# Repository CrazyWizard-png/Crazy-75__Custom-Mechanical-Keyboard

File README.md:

# Crazy-75
The journey of creating my first ever custom mechanical keyboard. 

Check my journal for the newest progress updates.

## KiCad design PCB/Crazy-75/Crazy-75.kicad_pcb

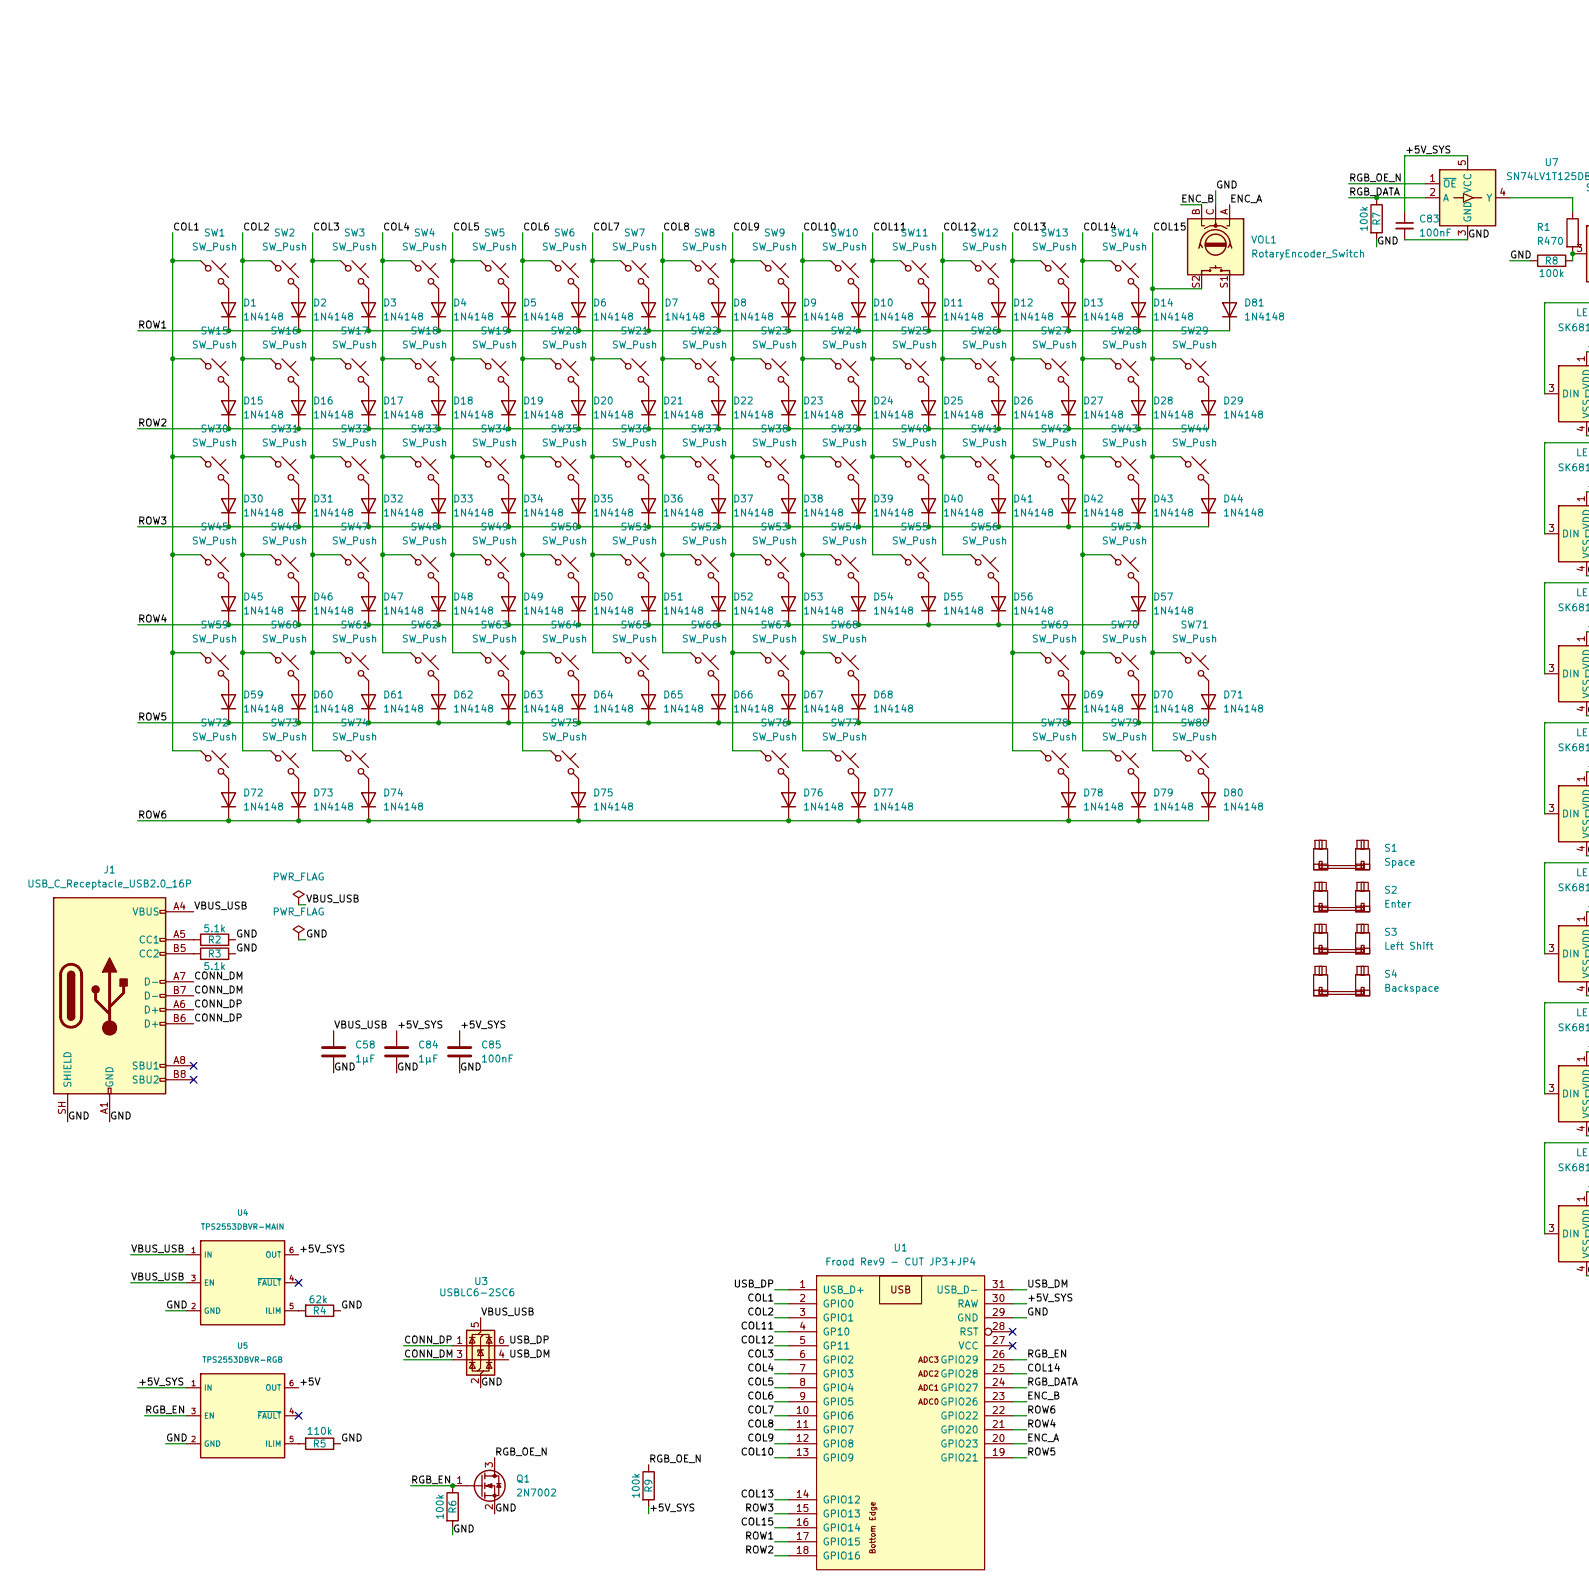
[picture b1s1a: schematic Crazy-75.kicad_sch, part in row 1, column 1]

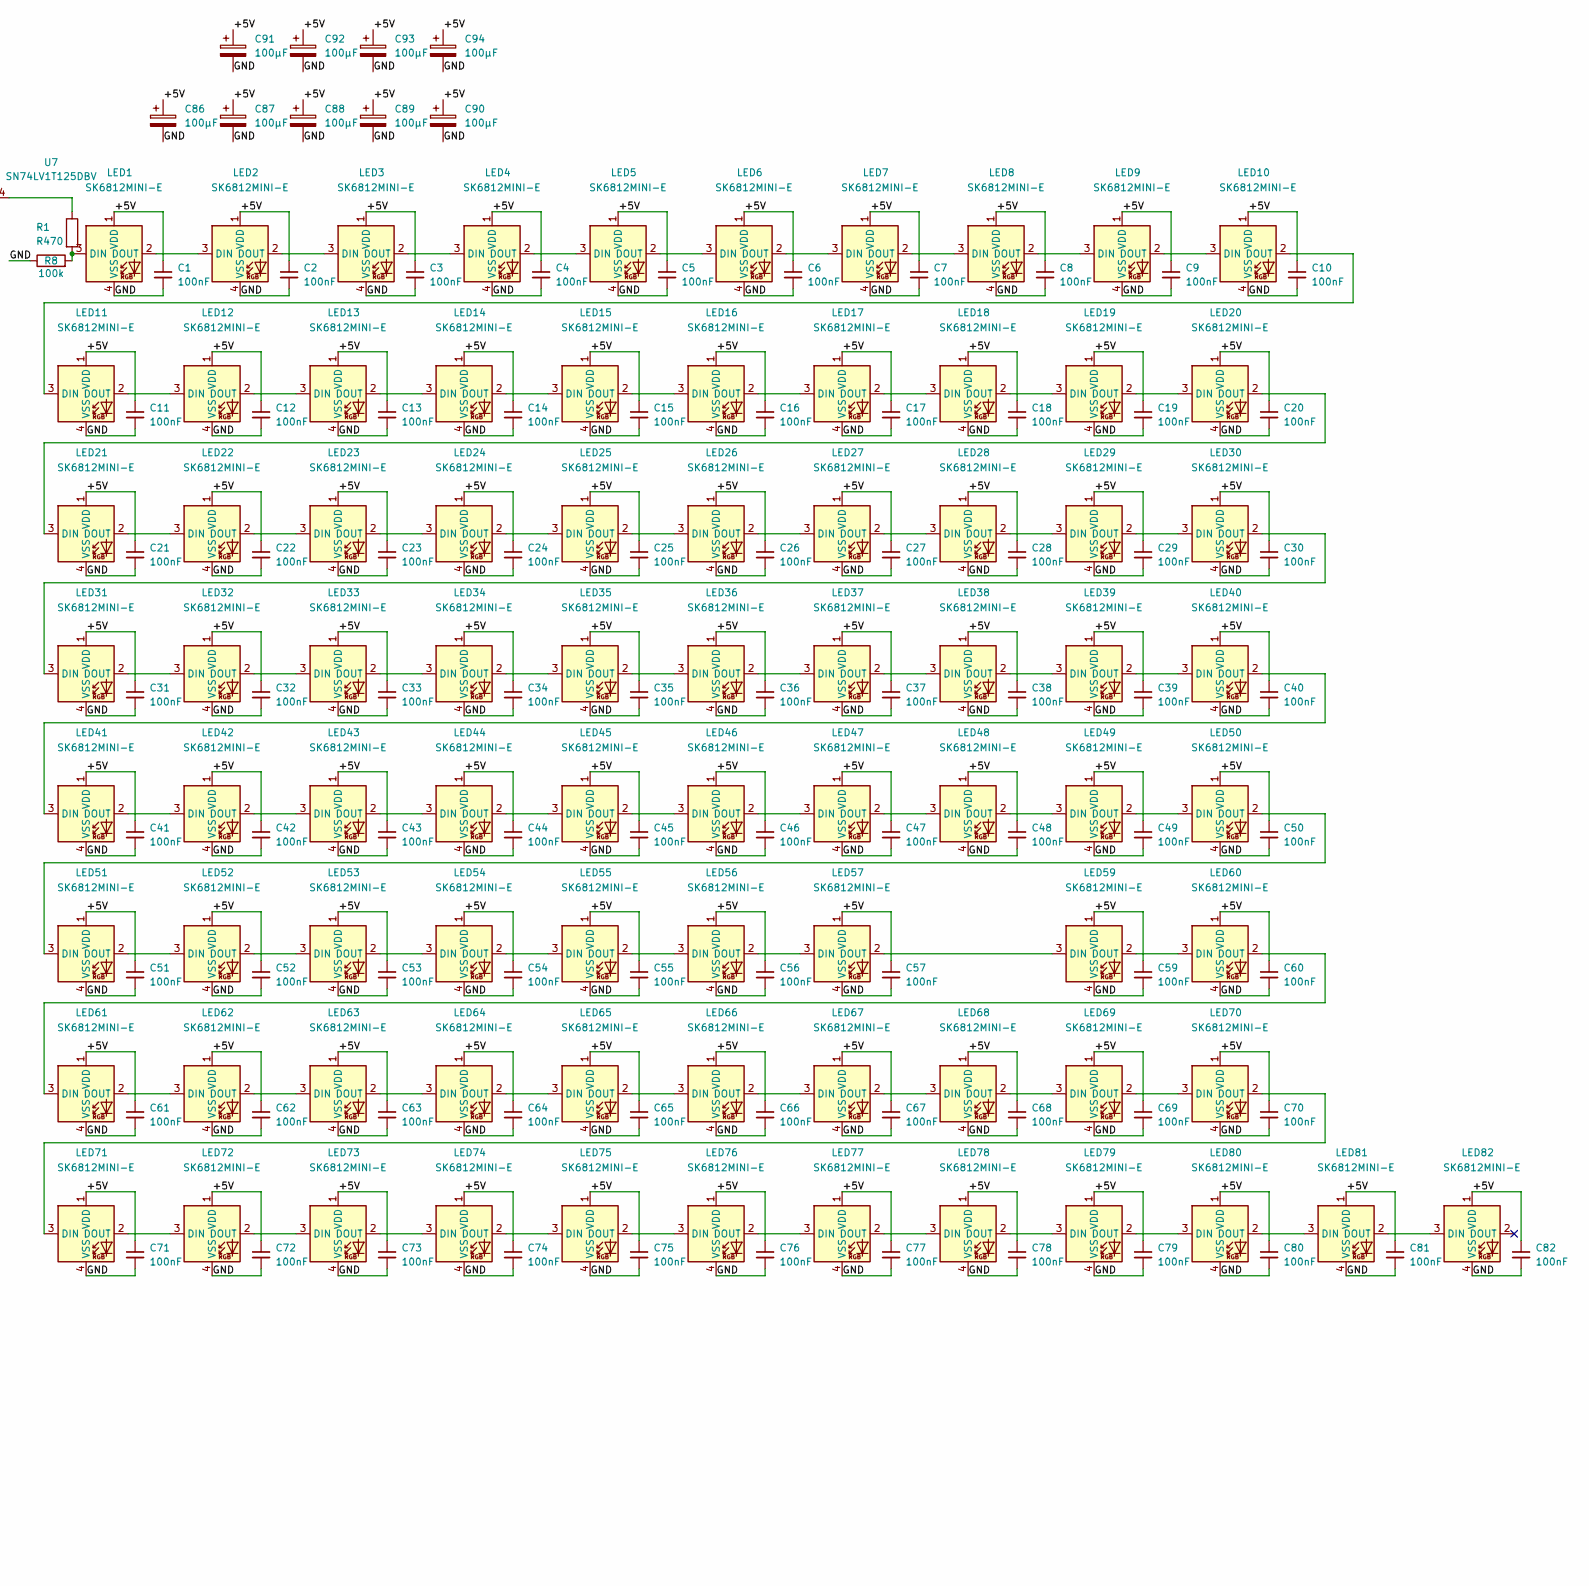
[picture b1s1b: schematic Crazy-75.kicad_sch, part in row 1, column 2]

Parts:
C1, C2, C3, C4, C5, C6, C7, C8, C9, C10, C11, C12, C13, C14, C15, C16, C17, C18, C19, C20, C21, C22, C23, C24, C25, C26, C27, C28, C29, C30, C31, C32, C33, C34, C35, C36, C37, C38, C39, C40, C41, C42, C43, C44, C45, C46, C47, C48, C49, C50, C51, C52, C53, C54, C55, C56, C57, C59, C60, C61, C62, C63, C64, C65, C66, C67, C68, C69, C70, C71, C72, C73, C74, C75, C76, C77, C78, C79, C80, C81, C82, C83, C85: 100nF; C_0805_2012Metric_Pad1.18x1.45mm_HandSolder
C58, C84: 1µF; C_0805_2012Metric_Pad1.18x1.45mm_HandSolder
C86, C87, C88, C89, C90, C91, C92, C93, C94: 100µF; CP_EIA-7343-31_Kemet-D_HandSolder
D1, D2, D3, D4, D5, D6, D7, D8, D9, D10, D11, D12, D13, D14, D15, D16, D17, D18, D19, D20, D21, D22, D23, D24, D25, D26, D27, D28, D29, D30, D31, D32, D33, D34, D35, D36, D37, D38, D39, D40, D41, D42, D43, D44, D45, D46, D47, D48, D49, D50, D51, D52, D53, D54, D55, D56, D57, D59, D60, D61, D62, D63, D64, D65, D66, D67, D68, D69, D70, D71, D72, D73, D74, D75, D76, D77, D78, D79, D80, D81: 1N4148; D_DO-35_SOD27_P7.62mm_Horizontal
J1: USB_C_Receptacle_USB2.0_16P; USB_C_Receptacle_GCT_USB4085
LED1, LED2, LED3, LED4, LED5, LED6, LED7, LED8, LED9, LED10, LED11, LED12, LED13, LED14, LED15, LED16, LED17, LED18, LED19, LED20, LED21, LED22, LED23, LED24, LED25, LED26, LED27, LED28, LED29, LED30, LED31, LED32, LED33, LED34, LED35, LED36, LED37, LED38, LED39, LED40, LED41, LED42, LED43, LED44, LED45, LED46, LED47, LED48, LED49, LED50, LED51, LED52, LED53, LED54, LED55, LED56, LED57, LED59, LED60, LED61, LED62, LED63, LED64, LED65, LED66, LED67, LED68, LED69, LED70, LED71, LED72, LED73, LED74, LED75, LED76, LED77, LED78, LED79, LED80, LED81, LED82: SK6812MINI-E; LED_MX_6028R
Q1: 2N7002; SOT-23_Handsoldering
R1: R470; R_Axial_DIN0207_L6.3mm_D2.5mm_P10.16mm_Horizontal
R2, R3: 5.1k; R_0805_2012Metric_Pad1.20x1.40mm_HandSolder
R4: 62k; R_0805_2012Metric_Pad1.20x1.40mm_HandSolder
R5: 110k; R_0805_2012Metric_Pad1.20x1.40mm_HandSolder
R6, R7, R8, R9: 100k; R_0805_2012Metric_Pad1.20x1.40mm_HandSolder
S1: Space; STAB_MX_P_6.25u
S2: Enter; STAB_MX_P_2.25u
S3: Left Shift; STAB_MX_P_2.25u
S4: Backspace; STAB_MX_P_2u
SW1, SW2, SW3, SW4, SW5, SW6, SW7, SW8, SW9, SW10, SW11, SW12, SW13, SW14, SW15, SW16, SW17, SW18, SW19, SW20, SW21, SW22, SW23, SW24, SW25, SW26, SW27, SW28, SW29, SW30, SW31, SW32, SW33, SW34, SW35, SW36, SW37, SW38, SW39, SW40, SW41, SW42, SW43, SW44, SW45, SW46, SW47, SW48, SW49, SW50, SW51, SW52, SW53, SW54, SW55, SW56, SW57, SW59, SW60, SW61, SW62, SW63, SW64, SW65, SW66, SW67, SW68, SW69, SW70, SW71, SW72, SW73, SW74, SW75, SW76, SW77, SW78, SW79, SW80: SW_Push; SW_MX_HS_CPG151101S11_1u
U1: Frood Rev9 - CUT JP3+JP4; Frood_Rev9_Carrier
U3: USBLC6-2SC6; SOT-23-6_Handsoldering
U4: TPS2553DBVR-MAIN; SOT-23-6_Handsoldering
U5: TPS2553DBVR-RGB; SOT-23-6_Handsoldering
U7: SN74LV1T125DBV; SOT-23-5_HandSoldering
VOL1: RotaryEncoder_Switch; RotaryEncoder_Alps_EC11E-Switch_Vertical_H20mm

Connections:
/+5V: C1.1, C2.1, C3.1, C4.1, C5.1, C6.1, C7.1, C8.1, C9.1, C10.1, C11.1, C12.1, C13.1, C14.1, C15.1, C16.1, C17.1, C18.1, C19.1, C20.1, C21.1, C22.1, C23.1, C24.1, C25.1, C26.1, C27.1, C28.1, C29.1, C30.1, C31.1, C32.1, C33.1, C34.1, C35.1, C36.1, C37.1, C38.1, C39.1, C40.1, C41.1, C42.1, C43.1, C44.1, C45.1, C46.1, C47.1, C48.1, C49.1, C50.1, C51.1, C52.1, C53.1, C54.1, C55.1, C56.1, C57.1, C59.1, C60.1, C61.1, C62.1, C63.1, C64.1, C65.1, C66.1, C67.1, C68.1, C69.1, C70.1, C71.1, C72.1, C73.1, C74.1, C75.1, C76.1, C77.1, C78.1, C79.1, C80.1, C81.1, C82.1, C86.1, C87.1, C88.1, C89.1, C90.1, C91.1, C92.1, C93.1, C94.1, LED1.1 (VDD), LED2.1 (VDD), LED3.1 (VDD), LED4.1 (VDD), LED5.1 (VDD), LED6.1 (VDD), LED7.1 (VDD), LED8.1 (VDD), LED9.1 (VDD), LED10.1 (VDD), LED11.1 (VDD), LED12.1 (VDD), LED13.1 (VDD), LED14.1 (VDD), LED15.1 (VDD), LED16.1 (VDD), LED17.1 (VDD), LED18.1 (VDD), LED19.1 (VDD), LED20.1 (VDD), LED21.1 (VDD), LED22.1 (VDD), LED23.1 (VDD), LED24.1 (VDD), LED25.1 (VDD), LED26.1 (VDD), LED27.1 (VDD), LED28.1 (VDD), LED29.1 (VDD), LED30.1 (VDD), LED31.1 (VDD), LED32.1 (VDD), LED33.1 (VDD), LED34.1 (VDD), LED35.1 (VDD), LED36.1 (VDD), LED37.1 (VDD), LED38.1 (VDD), LED39.1 (VDD), LED40.1 (VDD), LED41.1 (VDD), LED42.1 (VDD), LED43.1 (VDD), LED44.1 (VDD), LED45.1 (VDD), LED46.1 (VDD), LED47.1 (VDD), LED48.1 (VDD), LED49.1 (VDD), LED50.1 (VDD), LED51.1 (VDD), LED52.1 (VDD), LED53.1 (VDD), LED54.1 (VDD), LED55.1 (VDD), LED56.1 (VDD), LED57.1 (VDD), LED59.1 (VDD), LED60.1 (VDD), LED61.1 (VDD), LED62.1 (VDD), LED63.1 (VDD), LED64.1 (VDD), LED65.1 (VDD), LED66.1 (VDD), LED67.1 (VDD), LED68.1 (VDD), LED69.1 (VDD), LED70.1 (VDD), LED71.1 (VDD), LED72.1 (VDD), LED73.1 (VDD), LED74.1 (VDD), LED75.1 (VDD), LED76.1 (VDD), LED77.1 (VDD), LED78.1 (VDD), LED79.1 (VDD), LED80.1 (VDD), LED81.1 (VDD), LED82.1 (VDD), U5.6 (OUT)
/+5V_SYS: C83.1, C84.1, C85.1, R9.2, U1.30 (RAW), U4.6 (OUT), U5.1 (IN), U7.5 (VCC)
/COL1: SW1.1, SW15.1, SW30.1, SW45.1, SW59.1, SW72.1, U1.2 (GPIO0)
/COL2: SW2.1, SW16.1, SW31.1, SW46.1, SW60.1, SW73.1, U1.3 (GPIO1)
/COL3: SW3.1, SW17.1, SW32.1, SW47.1, SW61.1, SW74.1, U1.6 (GPIO2)
/COL4: SW4.1, SW18.1, SW33.1, SW48.1, SW62.1, U1.7 (GPIO3)
/COL5: SW5.1, SW19.1, SW34.1, SW49.1, SW63.1, U1.8 (GPIO4)
/COL6: SW6.1, SW20.1, SW35.1, SW50.1, SW64.1, SW75.1, U1.9 (GPIO5)
/COL7: SW7.1, SW21.1, SW36.1, SW51.1, SW65.1, U1.10 (GPIO6)
/COL8: SW8.1, SW22.1, SW37.1, SW52.1, SW66.1, U1.11 (GPIO7)
/COL9: SW9.1, SW23.1, SW38.1, SW53.1, SW67.1, SW76.1, U1.12 (GPIO8)
/COL10: SW10.1, SW24.1, SW39.1, SW54.1, SW68.1, SW77.1, U1.13 (GPIO9)
/COL11: SW11.1, SW25.1, SW40.1, SW55.1, U1.4 (GP10)
/COL12: SW12.1, SW26.1, SW41.1, SW56.1, U1.5 (GP11)
/COL13: SW13.1, SW27.1, SW42.1, SW69.1, SW78.1, U1.14 (GPIO12)
/COL14: SW14.1, SW28.1, SW43.1, SW57.1, SW70.1, SW79.1, U1.25 (GPIO28)
/COL15: SW29.1, SW44.1, SW71.1, SW80.1, U1.16 (GPIO14), VOL1.S2
/CONN_DM: J1.A7 (D-), J1.B7 (D-), U3.3 (I/O2)
/CONN_DP: J1.A6 (D+), J1.B6 (D+), U3.1 (I/O1)
/ENC_A: U1.20 (GPIO23), VOL1.A
/ENC_B: U1.23 (GPIO26), VOL1.B
/GND: C1.2, C2.2, C3.2, C4.2, C5.2, C6.2, C7.2, C8.2, C9.2, C10.2, C11.2, C12.2, C13.2, C14.2, C15.2, C16.2, C17.2, C18.2, C19.2, C20.2, C21.2, C22.2, C23.2, C24.2, C25.2, C26.2, C27.2, C28.2, C29.2, C30.2, C31.2, C32.2, C33.2, C34.2, C35.2, C36.2, C37.2, C38.2, C39.2, C40.2, C41.2, C42.2, C43.2, C44.2, C45.2, C46.2, C47.2, C48.2, C49.2, C50.2, C51.2, C52.2, C53.2, C54.2, C55.2, C56.2, C57.2, C58.2, C59.2, C60.2, C61.2, C62.2, C63.2, C64.2, C65.2, C66.2, C67.2, C68.2, C69.2, C70.2, C71.2, C72.2, C73.2, C74.2, C75.2, C76.2, C77.2, C78.2, C79.2, C80.2, C81.2, C82.2, C83.2, C84.2, C85.2, C86.2, C87.2, C88.2, C89.2, C90.2, C91.2, C92.2, C93.2, C94.2, J1.A1 (GND), J1.A12 (GND), J1.B1 (GND), J1.B12 (GND), J1.SH (SHIELD), LED1.4 (VSS), LED2.4 (VSS), LED3.4 (VSS), LED4.4 (VSS), LED5.4 (VSS), LED6.4 (VSS), LED7.4 (VSS), LED8.4 (VSS), LED9.4 (VSS), LED10.4 (VSS), LED11.4 (VSS), LED12.4 (VSS), LED13.4 (VSS), LED14.4 (VSS), LED15.4 (VSS), LED16.4 (VSS), LED17.4 (VSS), LED18.4 (VSS), LED19.4 (VSS), LED20.4 (VSS), LED21.4 (VSS), LED22.4 (VSS), LED23.4 (VSS), LED24.4 (VSS), LED25.4 (VSS), LED26.4 (VSS), LED27.4 (VSS), LED28.4 (VSS), LED29.4 (VSS), LED30.4 (VSS), LED31.4 (VSS), LED32.4 (VSS), LED33.4 (VSS), LED34.4 (VSS), LED35.4 (VSS), LED36.4 (VSS), LED37.4 (VSS), LED38.4 (VSS), LED39.4 (VSS), LED40.4 (VSS), LED41.4 (VSS), LED42.4 (VSS), LED43.4 (VSS), LED44.4 (VSS), LED45.4 (VSS), LED46.4 (VSS), LED47.4 (VSS), LED48.4 (VSS), LED49.4 (VSS), LED50.4 (VSS), LED51.4 (VSS), LED52.4 (VSS), LED53.4 (VSS), LED54.4 (VSS), LED55.4 (VSS), LED56.4 (VSS), LED57.4 (VSS), LED59.4 (VSS), LED60.4 (VSS), LED61.4 (VSS), LED62.4 (VSS), LED63.4 (VSS), LED64.4 (VSS), LED65.4 (VSS), LED66.4 (VSS), LED67.4 (VSS), LED68.4 (VSS), LED69.4 (VSS), LED70.4 (VSS), LED71.4 (VSS), LED72.4 (VSS), LED73.4 (VSS), LED74.4 (VSS), LED75.4 (VSS), LED76.4 (VSS), LED77.4 (VSS), LED78.4 (VSS), LED79.4 (VSS), LED80.4 (VSS), LED81.4 (VSS), LED82.4 (VSS), Q1.2 (S), R2.2, R3.2, R4.1, R5.1, R6.2, R7.2, R8.1, U1.29 (GND), U3.2 (GND), U4.2 (GND), U5.2 (GND), U7.3 (GND), VOL1.C
/RGB_DATA: R7.1, U1.24 (GPIO27), U7.2 (A)
/RGB_EN: Q1.1 (G), R6.1, U1.26 (GPIO29), U5.3 (EN)
/RGB_OE_N: Q1.3 (D), R9.1, U7.1 (~OE)
/ROW1: D1.1 (K), D2.1 (K), D3.1 (K), D4.1 (K), D5.1 (K), D6.1 (K), D7.1 (K), D8.1 (K), D9.1 (K), D10.1 (K), D11.1 (K), D12.1 (K), D13.1 (K), D14.1 (K), D81.1 (K), U1.17 (GPIO15)
/ROW2: D15.1 (K), D16.1 (K), D17.1 (K), D18.1 (K), D19.1 (K), D20.1 (K), D21.1 (K), D22.1 (K), D23.1 (K), D24.1 (K), D25.1 (K), D26.1 (K), D27.1 (K), D28.1 (K), D29.1 (K), U1.18 (GPIO16)
/ROW3: D30.1 (K), D31.1 (K), D32.1 (K), D33.1 (K), D34.1 (K), D35.1 (K), D36.1 (K), D37.1 (K), D38.1 (K), D39.1 (K), D40.1 (K), D41.1 (K), D42.1 (K), D43.1 (K), D44.1 (K), U1.15 (GPIO13)
/ROW4: D45.1 (K), D46.1 (K), D47.1 (K), D48.1 (K), D49.1 (K), D50.1 (K), D51.1 (K), D52.1 (K), D53.1 (K), D54.1 (K), D55.1 (K), D56.1 (K), D57.1 (K), U1.21 (GPIO20)
/ROW5: D59.1 (K), D60.1 (K), D61.1 (K), D62.1 (K), D63.1 (K), D64.1 (K), D65.1 (K), D66.1 (K), D67.1 (K), D68.1 (K), D69.1 (K), D70.1 (K), D71.1 (K), U1.19 (GPIO21)
/ROW6: D72.1 (K), D73.1 (K), D74.1 (K), D75.1 (K), D76.1 (K), D77.1 (K), D78.1 (K), D79.1 (K), D80.1 (K), U1.22 (GPIO22)
/USB_DM: U1.31 (USB_D-), U3.4 (I/O2)
/USB_DP: U1.1 (USB_D+), U3.6 (I/O1)
/VBUS_USB: C58.1, J1.A4 (VBUS), J1.A9 (VBUS), J1.B4 (VBUS), J1.B9 (VBUS), U3.5 (VBUS), U4.1 (IN), U4.3 (EN)
unnamed: D1.2 (A), SW1.2
unnamed: D2.2 (A), SW2.2
unnamed: D3.2 (A), SW3.2
unnamed: D4.2 (A), SW4.2
unnamed: D5.2 (A), SW5.2
unnamed: D6.2 (A), SW6.2
unnamed: D7.2 (A), SW7.2
unnamed: D8.2 (A), SW8.2
unnamed: D9.2 (A), SW9.2
unnamed: D10.2 (A), SW10.2
unnamed: D11.2 (A), SW11.2
unnamed: D12.2 (A), SW12.2
unnamed: D13.2 (A), SW13.2
unnamed: D14.2 (A), SW14.2
unnamed: D15.2 (A), SW15.2
unnamed: D16.2 (A), SW16.2
unnamed: D17.2 (A), SW17.2
unnamed: D18.2 (A), SW18.2
unnamed: D19.2 (A), SW19.2
unnamed: D20.2 (A), SW20.2
unnamed: D21.2 (A), SW21.2
unnamed: D22.2 (A), SW22.2
unnamed: D23.2 (A), SW23.2
unnamed: D24.2 (A), SW24.2
unnamed: D25.2 (A), SW25.2
unnamed: D26.2 (A), SW26.2
unnamed: D27.2 (A), SW27.2
unnamed: D28.2 (A), SW28.2
unnamed: D29.2 (A), SW29.2
unnamed: D30.2 (A), SW30.2
unnamed: D31.2 (A), SW31.2
unnamed: D32.2 (A), SW32.2
unnamed: D33.2 (A), SW33.2
unnamed: D34.2 (A), SW34.2
unnamed: D35.2 (A), SW35.2
unnamed: D36.2 (A), SW36.2
unnamed: D37.2 (A), SW37.2
unnamed: D38.2 (A), SW38.2
unnamed: D39.2 (A), SW39.2
unnamed: D40.2 (A), SW40.2
unnamed: D41.2 (A), SW41.2
unnamed: D42.2 (A), SW42.2
unnamed: D43.2 (A), SW43.2
unnamed: D44.2 (A), SW44.2
unnamed: D45.2 (A), SW45.2
unnamed: D46.2 (A), SW46.2
unnamed: D47.2 (A), SW47.2
unnamed: D48.2 (A), SW48.2
unnamed: D49.2 (A), SW49.2
unnamed: D50.2 (A), SW50.2
unnamed: D51.2 (A), SW51.2
unnamed: D52.2 (A), SW52.2
unnamed: D53.2 (A), SW53.2
unnamed: D54.2 (A), SW54.2
unnamed: D55.2 (A), SW55.2
unnamed: D56.2 (A), SW56.2
unnamed: D57.2 (A), SW57.2
unnamed: D59.2 (A), SW59.2
unnamed: D60.2 (A), SW60.2
unnamed: D61.2 (A), SW61.2
unnamed: D62.2 (A), SW62.2
unnamed: D63.2 (A), SW63.2
unnamed: D64.2 (A), SW64.2
unnamed: D65.2 (A), SW65.2
unnamed: D66.2 (A), SW66.2
unnamed: D67.2 (A), SW67.2
unnamed: D68.2 (A), SW68.2
unnamed: D69.2 (A), SW69.2
unnamed: D70.2 (A), SW70.2
unnamed: D71.2 (A), SW71.2
unnamed: D72.2 (A), SW72.2
unnamed: D73.2 (A), SW73.2
unnamed: D74.2 (A), SW74.2
unnamed: D75.2 (A), SW75.2
unnamed: D76.2 (A), SW76.2
unnamed: D77.2 (A), SW77.2
unnamed: D78.2 (A), SW78.2
unnamed: D79.2 (A), SW79.2
unnamed: D80.2 (A), SW80.2
unnamed: D81.2 (A), VOL1.S1
unnamed: J1.A5 (CC1), R2.1
unnamed: J1.B5 (CC2), R3.1
unnamed: LED1.3 (DIN), R1.2, R8.2
unnamed: LED1.2 (DOUT), LED2.3 (DIN)
unnamed: LED2.2 (DOUT), LED3.3 (DIN)
unnamed: LED3.2 (DOUT), LED4.3 (DIN)
unnamed: LED4.2 (DOUT), LED5.3 (DIN)
unnamed: LED5.2 (DOUT), LED6.3 (DIN)
unnamed: LED6.2 (DOUT), LED7.3 (DIN)
unnamed: LED7.2 (DOUT), LED8.3 (DIN)
unnamed: LED8.2 (DOUT), LED9.3 (DIN)
unnamed: LED9.2 (DOUT), LED10.3 (DIN)
unnamed: LED10.2 (DOUT), LED11.3 (DIN)
unnamed: LED11.2 (DOUT), LED12.3 (DIN)
unnamed: LED12.2 (DOUT), LED13.3 (DIN)
unnamed: LED13.2 (DOUT), LED14.3 (DIN)
unnamed: LED14.2 (DOUT), LED15.3 (DIN)
unnamed: LED15.2 (DOUT), LED16.3 (DIN)
unnamed: LED16.2 (DOUT), LED17.3 (DIN)
unnamed: LED17.2 (DOUT), LED18.3 (DIN)
unnamed: LED18.2 (DOUT), LED19.3 (DIN)
unnamed: LED19.2 (DOUT), LED20.3 (DIN)
unnamed: LED20.2 (DOUT), LED21.3 (DIN)
unnamed: LED21.2 (DOUT), LED22.3 (DIN)
unnamed: LED22.2 (DOUT), LED23.3 (DIN)
unnamed: LED23.2 (DOUT), LED24.3 (DIN)
unnamed: LED24.2 (DOUT), LED25.3 (DIN)
unnamed: LED25.2 (DOUT), LED26.3 (DIN)
unnamed: LED26.2 (DOUT), LED27.3 (DIN)
unnamed: LED27.2 (DOUT), LED28.3 (DIN)
unnamed: LED28.2 (DOUT), LED29.3 (DIN)
unnamed: LED29.2 (DOUT), LED30.3 (DIN)
unnamed: LED30.2 (DOUT), LED31.3 (DIN)
unnamed: LED31.2 (DOUT), LED32.3 (DIN)
unnamed: LED32.2 (DOUT), LED33.3 (DIN)
unnamed: LED33.2 (DOUT), LED34.3 (DIN)
unnamed: LED34.2 (DOUT), LED35.3 (DIN)
unnamed: LED35.2 (DOUT), LED36.3 (DIN)
unnamed: LED36.2 (DOUT), LED37.3 (DIN)
unnamed: LED37.2 (DOUT), LED38.3 (DIN)
unnamed: LED38.2 (DOUT), LED39.3 (DIN)
unnamed: LED39.2 (DOUT), LED40.3 (DIN)
unnamed: LED40.2 (DOUT), LED41.3 (DIN)
unnamed: LED41.2 (DOUT), LED42.3 (DIN)
unnamed: LED42.2 (DOUT), LED43.3 (DIN)
unnamed: LED43.2 (DOUT), LED44.3 (DIN)
unnamed: LED44.2 (DOUT), LED45.3 (DIN)
unnamed: LED45.2 (DOUT), LED46.3 (DIN)
unnamed: LED46.2 (DOUT), LED47.3 (DIN)
unnamed: LED47.2 (DOUT), LED48.3 (DIN)
unnamed: LED48.2 (DOUT), LED49.3 (DIN)
unnamed: LED49.2 (DOUT), LED50.3 (DIN)
unnamed: LED50.2 (DOUT), LED51.3 (DIN)
unnamed: LED51.2 (DOUT), LED52.3 (DIN)
unnamed: LED52.2 (DOUT), LED53.3 (DIN)
unnamed: LED53.2 (DOUT), LED54.3 (DIN)
unnamed: LED54.2 (DOUT), LED55.3 (DIN)
unnamed: LED55.2 (DOUT), LED56.3 (DIN)
unnamed: LED56.2 (DOUT), LED57.3 (DIN)
unnamed: LED57.2 (DOUT), LED59.3 (DIN)
unnamed: LED59.2 (DOUT), LED60.3 (DIN)
unnamed: LED60.2 (DOUT), LED61.3 (DIN)
unnamed: LED61.2 (DOUT), LED62.3 (DIN)
unnamed: LED62.2 (DOUT), LED63.3 (DIN)
unnamed: LED63.2 (DOUT), LED64.3 (DIN)
unnamed: LED64.2 (DOUT), LED65.3 (DIN)
unnamed: LED65.2 (DOUT), LED66.3 (DIN)
unnamed: LED66.2 (DOUT), LED67.3 (DIN)
unnamed: LED67.2 (DOUT), LED68.3 (DIN)
unnamed: LED68.2 (DOUT), LED69.3 (DIN)
unnamed: LED69.2 (DOUT), LED70.3 (DIN)
unnamed: LED70.2 (DOUT), LED71.3 (DIN)
unnamed: LED71.2 (DOUT), LED72.3 (DIN)
unnamed: LED72.2 (DOUT), LED73.3 (DIN)
unnamed: LED73.2 (DOUT), LED74.3 (DIN)
unnamed: LED74.2 (DOUT), LED75.3 (DIN)
unnamed: LED75.2 (DOUT), LED76.3 (DIN)
unnamed: LED76.2 (DOUT), LED77.3 (DIN)
unnamed: LED77.2 (DOUT), LED78.3 (DIN)
unnamed: LED78.2 (DOUT), LED79.3 (DIN)
unnamed: LED79.2 (DOUT), LED80.3 (DIN)
unnamed: LED80.2 (DOUT), LED81.3 (DIN)
unnamed: LED81.2 (DOUT), LED82.3 (DIN)
unnamed: R4.2, U4.5 (ILIM)
unnamed: R5.2, U5.5 (ILIM)
unnamed: R1.1, U7.4 (Y)

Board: 2 copper layers, 355 parts (261 on the bottom side), 200 nets, no tracks yet.
